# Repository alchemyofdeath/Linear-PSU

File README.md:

# Linear-PSU
Adjustable current linear power supply

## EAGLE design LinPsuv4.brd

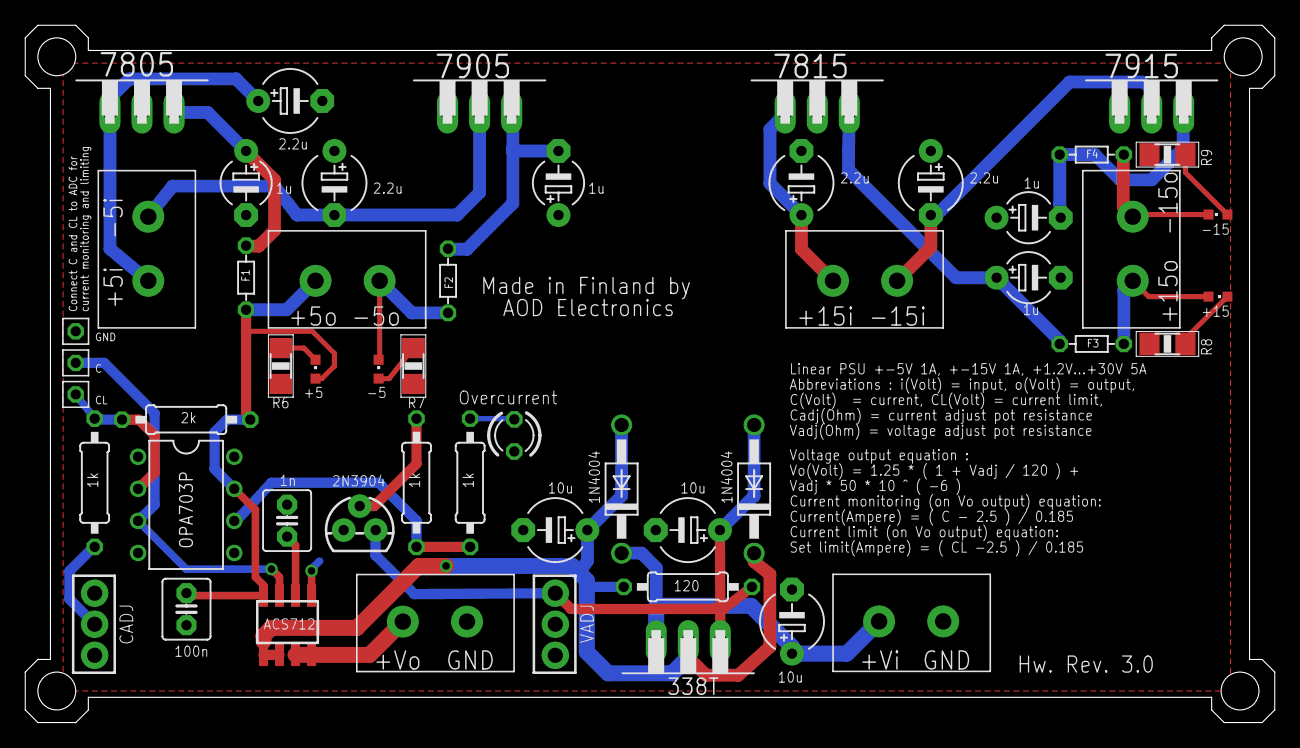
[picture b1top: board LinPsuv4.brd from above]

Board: 2 copper layers, 99.0 x 55.2 mm, 52 parts (0 on the bottom side), 28 nets.

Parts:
2N3904: TO-92
7805: 7805; TO220H
7815: 7815T; TO220H
7905, 7915: TO220H
+5, +15: CHIPLED_0603
-5, -15: CHIPLED_0603
C1, C3, C5, C7: 2.2u; E5-5
C2, C4, C6, C8: 1u; E5-4
C9, C10, C11: 10u; E5-5
C12: 100n; C2.5-4
C13: 1n; C2.5-4
CADJ: 3RP/1610N
D1, D2: 1N4004; DO41-10
F1, F2, F3, F4: THERMISTOR-5; R-5
IC2: ACS712; SO08
IC3: 338T; TO220H
IC5: OPA703P; DIL08
IN5V, IN15V: 1X2_5MM
LED1: LED3MM
OUT5V, OUT15V: 1X2_5MM
R1: 120; 0207/10
R2, R4, R5: 1k; 0207/10
R3: 2k; 0207/10
R6, R7, R8, R9: R1206
U$1: C; DORU_CON_1X1
U$2: CL; DORU_CON_1X1
U$3: GND; DORU_CON_1X1
U$5, U$6: 1X2_5MM
VADJ: 3RP/1610N

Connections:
5VIN: 7805.1, C3.+, IN5V.IN1
5VOUT: +5.A, C12.1, F1.2, IC2.8, IC5.7, OUT5V.IN1, R3.2
15VIN: 7815.1, C7.+, IN15V.IN1
15VOUT: +15.A, F3.2, OUT15V.IN1
174243: 7915.3, C6.-, F4.2
35353535: 7815.3, C8.+, F3.1
-5VIN: 7905.2, C1.-, IN5V.IN2
-5VOUT: -5.C, F2.1, OUT5V.IN2
-15VIN: 7915.2, C5.-, IN15V.IN2
-15VOUT: -15.C, F4.1, OUT15V.IN2
ADJ: 2N3904.3, C9.+, D1.A, IC3.1, R1.1, VADJ.1
COUT: IC2.7, IC5.3, U$1.PIN1
CSET: IC5.2, R2.2, R3.1, U$2.PIN1
GND: 2N3904.1, 7805.2, 7815.2, 7905.1, 7915.1, C1.+, C2.+, C3.-, C4.-, C5.+, C6.+, C7.-, C8.-, C9.-, C10.-, C11.-, C12.2, C13.2, CADJ.3, IC2.5, IC5.4, LED1.K, R6.1, R7.1, R8.1, R9.1, U$3.PIN1, U$5.IN1, U$6.IN1, VADJ.2
N#%#: 7805.3, C4.+, F1.1
unnamed: C11.+, D2.C, IC3.3, U$5.IN2
unnamed: +15.C, R8.2
unnamed: LED1.A, R4.1
unnamed: IC5.6, R4.2, R5.2
unnamed: C13.1, IC2.6
unnamed: IC2.3, IC2.4, U$6.IN2
unnamed: +5.C, R6.2
unnamed: -15.A, R9.2
unnamed: CADJ.2, R2.1
unnamed: 2N3904.2, R5.1
unnamed: -5.A, R7.2
R35353: 7905.3, C2.-, F2.2
VOUTADJ: C10.+, D1.C, D2.A, IC2.1, IC2.2, IC3.2, R1.2

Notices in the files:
parts and their libraries:
SparkFun-DiscreteSemi: Licensing: Creative Commons ShareAlike 4.0 International - https://creativecommons.org/licenses/by-sa/4.0
